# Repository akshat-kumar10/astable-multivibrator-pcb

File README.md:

# Astable Multivibrator (NE555 Timer)

A through-hole KiCad project implementing an astable multivibrator using a NE555 timer in DIP-8 format. The board generates a blinking output signal and includes an LED indicator plus external terminal connections for power and signal output.

## Overview

- **Circuit type:** Astable multivibrator
- **IC:** NE555P (DIP-8)
- **Supply:** DC power input via 2-pin terminal block (J1)
- **Output:** 2-pin terminal block (J2) provides the NE555 output and ground reference
- **Board type:** 2-layer PCB, 1.6 mm thickness, through-hole components

## Key Components

- `U1` — NE555P timer, `Package_DIP:DIP-8_W7.62mm`
- `R1` — 2 kΩ resistor, `Resistor_THT:R_Axial_DIN0207_L6.3mm_D2.5mm_P7.62mm_Horizontal`
- `R2` — 146 kΩ resistor, `Resistor_THT:R_Axial_DIN0207_L6.3mm_D2.5mm_P7.62mm_Horizontal`
- `R3` — 560 Ω resistor, `Resistor_THT:R_Axial_DIN0207_L6.3mm_D2.5mm_P7.62mm_Horizontal`
- `C1` — 10 µF electrolytic capacitor, `Capacitor_THT:CP_Radial_D5.0mm_P2.00mm`
- `C2` — 0.1 µF bypass capacitor, `Capacitor_THT:C_Disc_D5.0mm_W2.5mm_P5.00mm`
- `D1` — LED indicator, `LED_THT:LED_D5.0mm`
- `J1` — 2-pin Phoenix terminal block for power input, `TerminalBlock_Phoenix:TerminalBlock_Phoenix_MKDS-1,5-2-5.08mm_Horizontal`
- `J2` — 2-pin Phoenix terminal block for output and ground, same footprint as `J1`

## Connector Pinout

- `J1` — Power input
  - Pin 1: `GND`
  - Pin 2: `VCC`
- `J2` — Output terminal
  - Pin 1: `Output` (NE555 pin 3)
  - Pin 2: `GND`

## Project Files

- `Astable_Multivibrator.kicad_sch` — Schematic file
- `Astable_Multivibrator.kicad_pcb` — PCB layout file
- `Astable_Multivibrator.kicad_prl` — PCB print settings
- `Astable_Multivibrator.kicad_pro` — Project settings
- `DRC.rpt` — Design rule check report
- `report.txt` — Schematic validation / netlist report
- `Gerbers/` — Generated Gerber outputs for fabrication
- `Gerbers.zip` — Archive of the Gerber files

## Usage

1. Open `Astable_Multivibrator.pro` in KiCad (recommended KiCad 10 or later).
2. Review the schematic and PCB layout for your chosen component footprints.
3. Run ERC in Eeschema and DRC in Pcbnew before fabrication.
4. Export Gerbers from the `Gerbers/` folder or regenerate them as needed.

## Notes

- The board is designed for standard through-hole assembly.
- Component placement and routing are built for a simple low-frequency blinking oscillator.
- Verify supply voltage compatibility for the NE555 and LED before connecting power.

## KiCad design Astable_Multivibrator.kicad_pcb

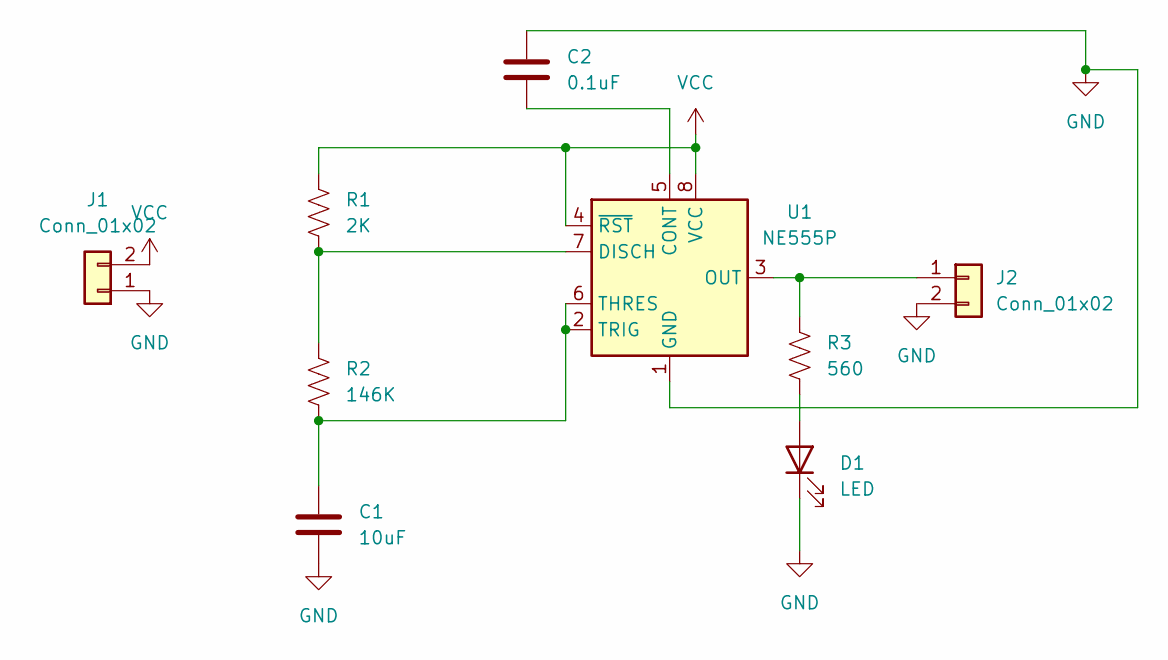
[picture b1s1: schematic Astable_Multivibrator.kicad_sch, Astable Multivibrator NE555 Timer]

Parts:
C1: 10uF; CP_Radial_D5.0mm_P2.00mm
C2: 0.1uF; C_Disc_D5.0mm_W2.5mm_P5.00mm
D1: LED; LED_D5.0mm
J1, J2: Conn_01x02; TerminalBlock_Phoenix_MKDS-1,5-2-5.08_1x02_P5.08mm_Horizont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
R1: 2K; R_Axial_DIN0207_L6.3mm_D2.5mm_P7.62mm_Horizontal
R2: 146K; R_Axial_DIN0207_L6.3mm_D2.5mm_P7.62mm_Horizontal
R3: 560; R_Axial_DIN0207_L6.3mm_D2.5mm_P7.62mm_Horizontal
U1: NE555P; DIP-8_W7.62mm

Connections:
GND: C1.2, C2.1, D1.1 (K), J1.1, J2.2, U1.1 (GND)
unnamed: D1.2 (A), R3.2
unnamed: J2.1, R3.1, U1.3 (OUT)
unnamed: C2.2, U1.5 (CONT)
unnamed: R1.2, R2.1, U1.7 (DISCH)
unnamed: C1.1, R2.2, U1.2 (TRIG), U1.6 (THRES)
VCC: J1.2, R1.1, U1.4 (~RST), U1.8 (VCC)

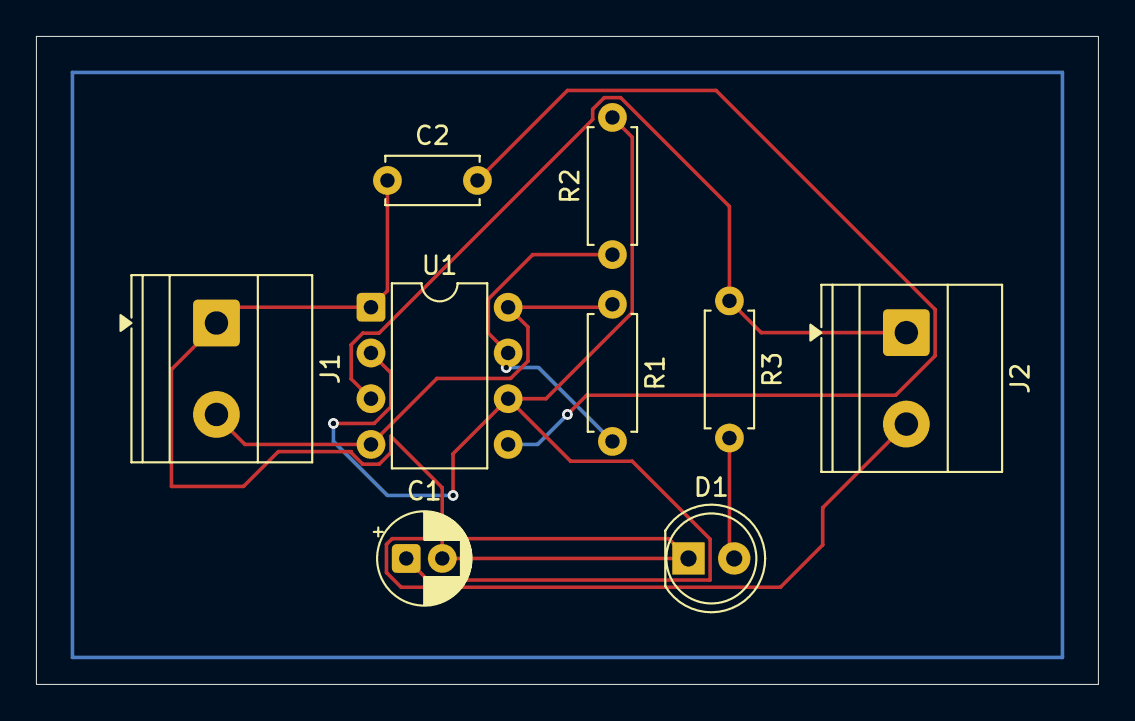
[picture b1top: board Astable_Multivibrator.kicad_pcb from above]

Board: 2 copper layers, 59.0 x 36.0 mm, 9 parts (0 on the bottom side), 7 nets.

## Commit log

2026-05-19 Initial commit: Completed NE555 astable multivibrator schematic and PCB layout
2026-05-19 Replace PCB image with HTML img tag
    Updated image format for the 3D model of PCB in README.
